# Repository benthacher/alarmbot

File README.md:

# Alarmbot project

## Alarmbot PCB

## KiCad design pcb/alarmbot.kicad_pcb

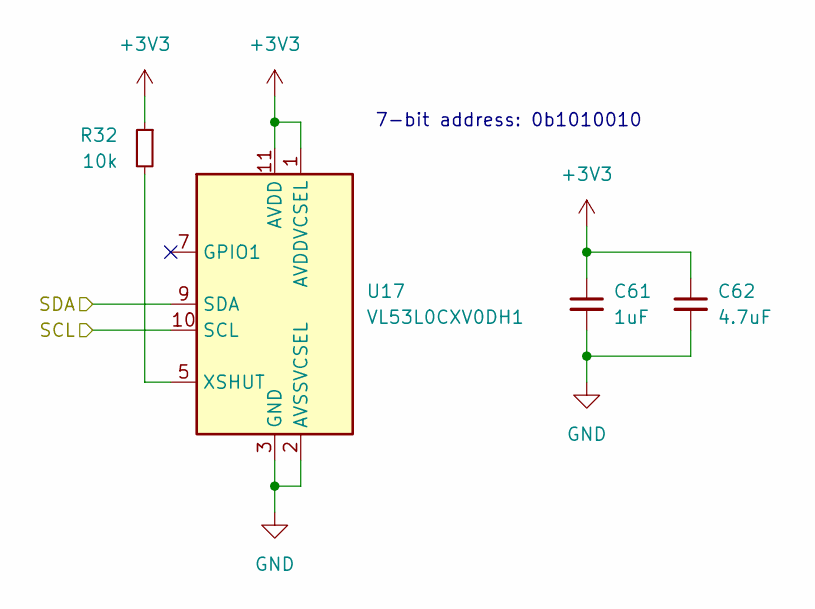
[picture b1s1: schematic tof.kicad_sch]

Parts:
C61: 1uF; C_0402_1005Metric; LCSC C52923
C62: 4.7uF; C_0402_1005Metric; LCSC C23733
R32: 10k; R_0402_1005Metric; LCSC C25744
U17: VL53L0CXV0DH1; ST_VL53L1x; LCSC C91199

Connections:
+3V3: C61.1, C62.1, R32.1, U17.1 (AVDDVCSEL), U17.11 (AVDD); also elsewhere on the board
/MCU/I2C2_SCL: U17.10 (SCL); also elsewhere on the board
/MCU/I2C2_SDA: U17.9 (SDA); also elsewhere on the board
GND: C61.2, C62.2, U17.2 (AVSSVCSEL), U17.3 (GND), U17.4 (GND), U17.6 (GND), U17.12 (GND); also elsewhere on the board
unnamed: R32.2, U17.5 (XSHUT)

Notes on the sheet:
7-bit address: 0b1010010

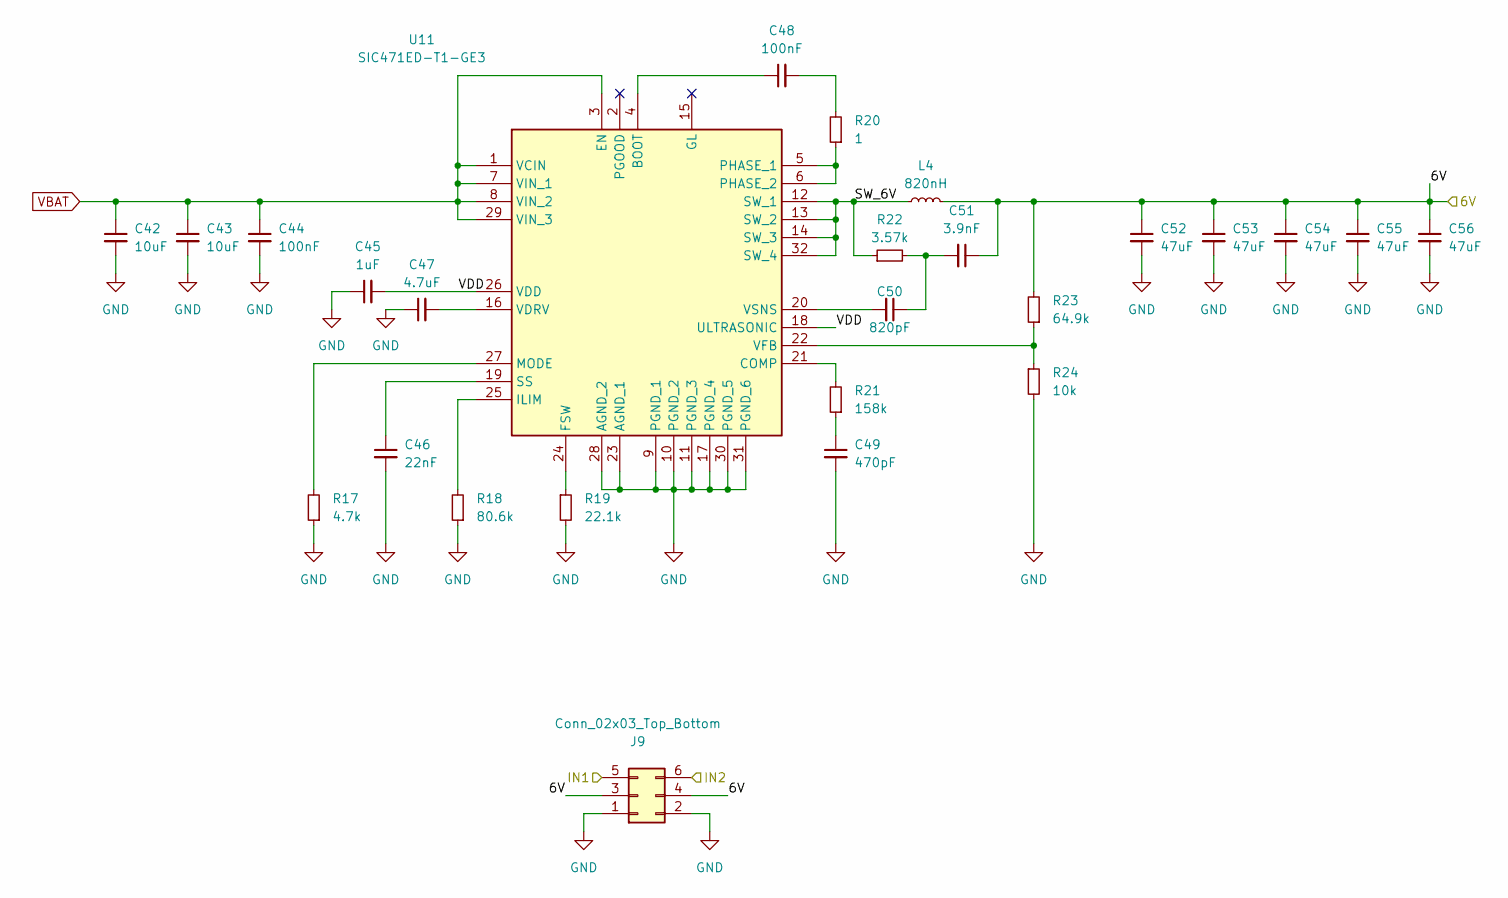
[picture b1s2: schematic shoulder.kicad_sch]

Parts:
C42, C43: 10uF; C_1206_3216Metric; LCSC C13585
C44, C48: 100nF; C_0402_1005Metric; Voltage 50V; LCSC C307331
C45: 1uF; C_0402_1005Metric; LCSC C52923
C46: 22nF; C_0402_1005Metric; LCSC C1532
C47: 4.7uF; C_0402_1005Metric; LCSC C23733
C49: 470pF; C_0402_1005Metric; LCSC C1537
C50: 820pF; C_0402_1005Metric; LCSC C107031
C51: 3.9nF; C_0402_1005Metric; LCSC C45188
C52, C53, C54, C55, C56: 47uF; C_1210_3225Metric; LCSC C5440143
J9: Conn_02x03_Top_Bottom; PinHeader_2x03_P2.54mm_Vertical
L4: 820nH; CMPI1040; LCSC C7588944
R17: 4.7k; R_0402_1005Metric; LCSC C25900
R18: 80.6k; R_0402_1005Metric; LCSC C25921
R19: 22.1k; R_0402_1005Metric; LCSC C43473
R20: 1; R_0402_1005Metric; LCSC C25086
R21: 158k; R_0402_1005Metric; LCSC C185464
R22: 3.57k; R_0402_1005Metric; LCSC C3037168
R23: 64.9k; R_0402_1005Metric; LCSC C5713275
R24: 10k; R_0402_1005Metric; LCSC C25744
U11: SIC471ED-T1-GE3; SIC471EDT1GE3; Manufacturer_Part_Number SIC471ED-T1-GE3; Mouser Part Number 78-SIC471ED-T1-GE3

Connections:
/MCU/TIM2_CH1: J9.5; also elsewhere on the board
/MCU/TIM2_CH2: J9.6; also elsewhere on the board
/Shoulder1/6V: C51.1, C52.1, C53.1, C54.1, C55.1, C56.1, J9.3, J9.4, L4.2, R23.2
/Shoulder1/SW_6V: L4.1, R22.1, U11.12 (SW_1), U11.13 (SW_2), U11.14 (SW_3), U11.32 (SW_4)
/Shoulder1/VDD: C45.2, U11.18 (ULTRASONIC), U11.26 (VDD)
GND: C42.2, C43.2, C44.2, C45.1, C46.2, C47.1, C49.2, C52.2, C53.2, C54.2, C55.2, C56.2, J9.1, J9.2, R17.1, R18.1, R19.2, R24.2, U11.9 (PGND_1), U11.10 (PGND_2), U11.11 (PGND_3), U11.17 (PGND_4), U11.23 (AGND_1), U11.28 (AGND_2), U11.30 (PGND_5), U11.31 (PGND_6); also elsewhere on the board
unnamed: C48.2, R20.2
unnamed: C49.1, R21.1
unnamed: C50.1, C51.2, R22.2
unnamed: C48.1, U11.4 (BOOT)
unnamed: R21.2, U11.21 (COMP)
unnamed: R19.1, U11.24 (FSW)
unnamed: R18.2, U11.25 (ILIM)
unnamed: R17.2, U11.27 (MODE)
unnamed: R20.1, U11.5 (PHASE_1), U11.6 (PHASE_2)
unnamed: C46.1, U11.19 (SS)
unnamed: C47.2, U11.16 (VDRV)
unnamed: R23.1, R24.1, U11.22 (VFB)
unnamed: C50.2, U11.20 (VSNS)
VBAT: C42.1, C43.1, C44.1, U11.1 (VCIN), U11.3 (EN), U11.7 (VIN_1), U11.8 (VIN_2), U11.29 (VIN_3); also elsewhere on the board

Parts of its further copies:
C63, C64, C78, C79, C93, C94: 10uF; C_1206_3216Metric; LCSC C13585
C65, C69, C80, C84, C95, C99: 100nF; C_0402_1005Metric; Voltage 50V; LCSC C307331
C66, C81, C96: 1uF; C_0402_1005Metric; LCSC C52923
C67, C82, C97: 22nF; C_0402_1005Metric; LCSC C1532
C68, C83, C98: 4.7uF; C_0402_1005Metric; LCSC C23733
C70, C85, C100: 470pF; C_0402_1005Metric; LCSC C1537
C71, C86, C101: 820pF; C_0402_1005Metric; LCSC C107031
C72, C87, C102: 3.9nF; C_0402_1005Metric; LCSC C45188
C73, C74, C75, C76, C77, C88, C89, C90, C91, C92, C103, C104, C105, C106, C107: 47uF; C_1210_3225Metric; LCSC C5440143
J13, J14, J15: Conn_02x03_Top_Bottom; PinHeader_2x03_P2.54mm_Vertical
L5, L6, L7: 820nH; CMPI1040; LCSC C7588944
R33, R41, R49: 4.7k; R_0402_1005Metric; LCSC C25900
R34, R42, R50: 80.6k; R_0402_1005Metric; LCSC C25921
R35, R43, R51: 22.1k; R_0402_1005Metric; LCSC C43473
R36, R44, R52: 1; R_0402_1005Metric; LCSC C25086
R37, R45, R53: 158k; R_0402_1005Metric; LCSC C185464
R38, R46, R54: 3.57k; R_0402_1005Metric; LCSC C3037168
R39, R47, R55: 64.9k; R_0402_1005Metric; LCSC C5713275
R40, R48, R56: 10k; R_0402_1005Metric; LCSC C25744
U18, U19, U20: SIC471ED-T1-GE3; SIC471EDT1GE3; Manufacturer_Part_Number SIC471ED-T1-GE3; Mouser Part Number 78-SIC471ED-T1-GE3

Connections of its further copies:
/MCU/TIM1_CH1: J14.5; also elsewhere on the board
/MCU/TIM1_CH2: J14.6; also elsewhere on the board
/MCU/TIM1_CH3: J15.5; also elsewhere on the board
/MCU/TIM1_CH4: J15.6; also elsewhere on the board
/MCU/TIM2_CH3: J13.5; also elsewhere on the board
/MCU/TIM2_CH4: J13.6; also elsewhere on the board
/Shoulder2/6V: C72.1, C73.1, C74.1, C75.1, C76.1, C77.1, J13.3, J13.4, L5.2, R39.2; also elsewhere on the board
/Shoulder2/SW_6V: L5.1, R38.1, U18.12 (SW_1), U18.13 (SW_2), U18.14 (SW_3), U18.32 (SW_4)
/Shoulder2/VDD: C66.2, U18.18 (ULTRASONIC), U18.26 (VDD)
/Shoulder3/6V: C87.1, C88.1, C89.1, C90.1, C91.1, C92.1, J14.3, J14.4, L6.2, R47.2
/Shoulder3/SW_6V: L6.1, R46.1, U19.12 (SW_1), U19.13 (SW_2), U19.14 (SW_3), U19.32 (SW_4)
/Shoulder3/VDD: C81.2, U19.18 (ULTRASONIC), U19.26 (VDD)
/Shoulder4/6V: C102.1, C103.1, C104.1, C105.1, C106.1, C107.1, J15.3, J15.4, L7.2, R55.2; also elsewhere on the board
/Shoulder4/SW_6V: L7.1, R54.1, U20.12 (SW_1), U20.13 (SW_2), U20.14 (SW_3), U20.32 (SW_4)
/Shoulder4/VDD: C96.2, U20.18 (ULTRASONIC), U20.26 (VDD)
GND: C63.2, C64.2, C65.2, C66.1, C67.2, C68.1, C70.2, C73.2, C74.2, C75.2, C76.2, C77.2, C78.2, C79.2, C80.2, C81.1, C82.2, C83.1, C85.2, C88.2, C89.2, C90.2, C91.2, C92.2, C93.2, C94.2, C95.2, C96.1, C97.2, C98.1, C100.2, C103.2, C104.2, C105.2, C106.2, C107.2, J13.1, J13.2, J14.1, J14.2, J15.1, J15.2, R33.1, R34.1, R35.2, R40.2, R41.1, R42.1, R43.2, R48.2, R49.1, R50.1, R51.2, R56.2, U18.9 (PGND_1), U18.10 (PGND_2), U18.11 (PGND_3), U18.17 (PGND_4), U18.23 (AGND_1), U18.28 (AGND_2), U18.30 (PGND_5), U18.31 (PGND_6), U19.9 (PGND_1), U19.10 (PGND_2), U19.11 (PGND_3), U19.17 (PGND_4), U19.23 (AGND_1), U19.28 (AGND_2), U19.30 (PGND_5), U19.31 (PGND_6), U20.9 (PGND_1), U20.10 (PGND_2), U20.11 (PGND_3), U20.17 (PGND_4), U20.23 (AGND_1), U20.28 (AGND_2), U20.30 (PGND_5), U20.31 (PGND_6); also elsewhere on the board
unnamed: C69.2, R36.2
unnamed: C70.1, R37.1
unnamed: C71.1, C72.2, R38.2
unnamed: C84.2, R44.2
unnamed: C85.1, R45.1
unnamed: C86.1, C87.2, R46.2
unnamed: C99.2, R52.2
unnamed: C100.1, R53.1
unnamed: C101.1, C102.2, R54.2
unnamed: C69.1, U18.4 (BOOT)
unnamed: R37.2, U18.21 (COMP)
unnamed: R35.1, U18.24 (FSW)
unnamed: R34.2, U18.25 (ILIM)
unnamed: R33.2, U18.27 (MODE)
unnamed: R36.1, U18.5 (PHASE_1), U18.6 (PHASE_2)
unnamed: C67.1, U18.19 (SS)
unnamed: C68.2, U18.16 (VDRV)
unnamed: R39.1, R40.1, U18.22 (VFB)
unnamed: C71.2, U18.20 (VSNS)
unnamed: C84.1, U19.4 (BOOT)
unnamed: R45.2, U19.21 (COMP)
unnamed: R43.1, U19.24 (FSW)
unnamed: R42.2, U19.25 (ILIM)
unnamed: R41.2, U19.27 (MODE)
unnamed: R44.1, U19.5 (PHASE_1), U19.6 (PHASE_2)
unnamed: C82.1, U19.19 (SS)
unnamed: C83.2, U19.16 (VDRV)
unnamed: R47.1, R48.1, U19.22 (VFB)
unnamed: C86.2, U19.20 (VSNS)
unnamed: C99.1, U20.4 (BOOT)
unnamed: R53.2, U20.21 (COMP)
unnamed: R51.1, U20.24 (FSW)
unnamed: R50.2, U20.25 (ILIM)
unnamed: R49.2, U20.27 (MODE)
unnamed: R52.1, U20.5 (PHASE_1), U20.6 (PHASE_2)
unnamed: C97.1, U20.19 (SS)
unnamed: C98.2, U20.16 (VDRV)
unnamed: R55.1, R56.1, U20.22 (VFB)
unnamed: C101.2, U20.20 (VSNS)
VBAT: C63.1, C64.1, C65.1, C78.1, C79.1, C80.1, C93.1, C94.1, C95.1, U18.1 (VCIN), U18.3 (EN), U18.7 (VIN_1), U18.8 (VIN_2), U18.29 (VIN_3), U19.1 (VCIN), U19.3 (EN), U19.7 (VIN_1), U19.8 (VIN_2), U19.29 (VIN_3), U20.1 (VCIN), U20.3 (EN), U20.7 (VIN_1), U20.8 (VIN_2), U20.29 (VIN_3); also elsewhere on the board

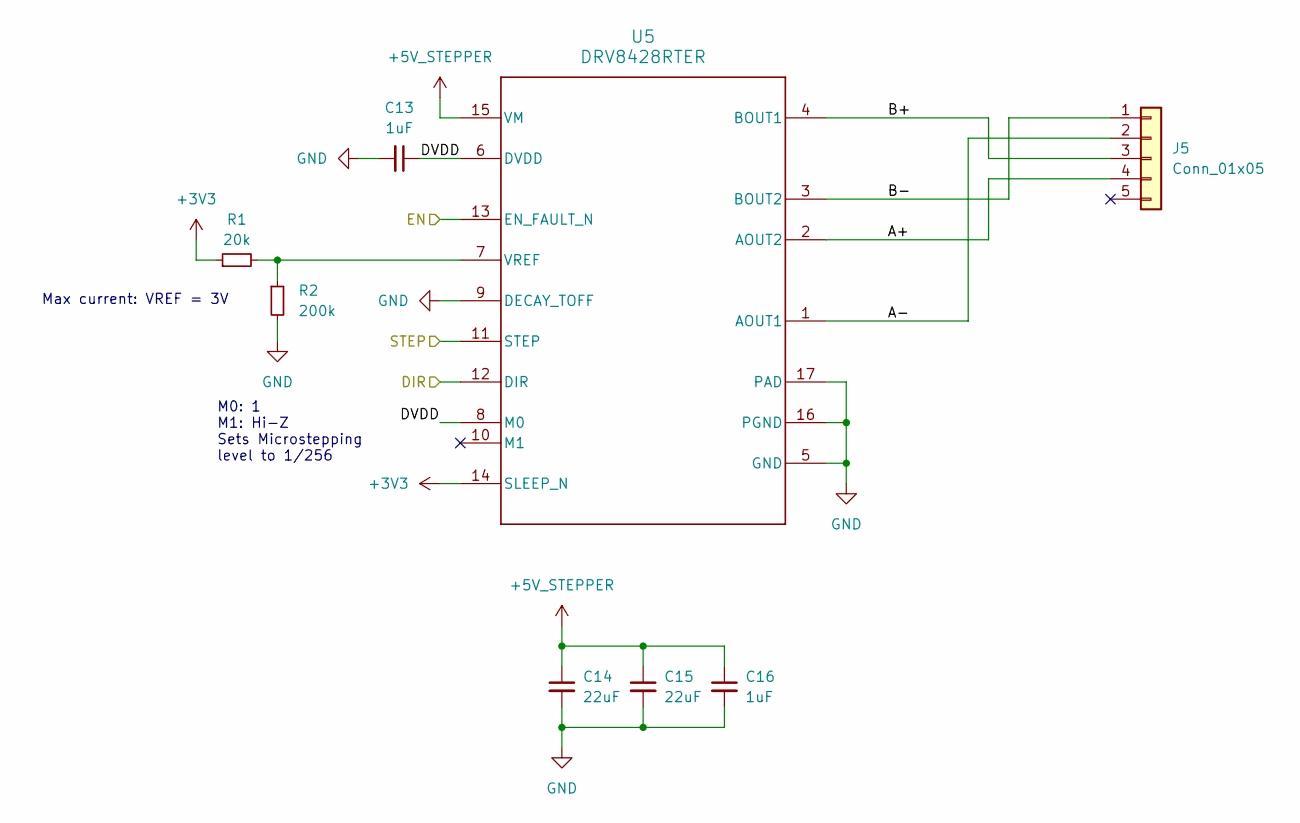
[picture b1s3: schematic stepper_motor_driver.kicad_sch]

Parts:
C13, C16: 1uF; C_0402_1005Metric; LCSC C52923
C14, C15: 22uF; C_1206_3216Metric; LCSC C12891
J5: Conn_01x05; JST_XH_B5B-XH-A_1x05_P2.50mm_Vertical
R1: 20k; R_0402_1005Metric; LCSC C25765
R2: 200k; R_0402_1005Metric; LCSC C25764
U5: DRV8428RTER; RTE0016J; LCSC C2857955

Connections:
+3V3: R1.1, U5.14 (SLEEP_N); also elsewhere on the board
+5V_STEPPER: C14.1, C15.1, C16.1, U5.15 (VM); also elsewhere on the board
/MCU/HEAD_PITCH_DIR: U5.12 (DIR); also elsewhere on the board
/MCU/HEAD_PITCH_EN: U5.13 (EN_FAULT_N); also elsewhere on the board
/MCU/TIM17_CH1: U5.11 (STEP); also elsewhere on the board
/Stepper1/A+: J5.4, U5.2 (AOUT2)
/Stepper1/A-: J5.2, U5.1 (AOUT1)
/Stepper1/B+: J5.3, U5.4 (BOUT1)
/Stepper1/B-: J5.1, U5.3 (BOUT2)
/Stepper1/DVDD: C13.1, U5.6 (DVDD), U5.8 (M0)
GND: C13.2, C14.2, C15.2, C16.2, R2.2, U5.5 (GND), U5.9 (DECAY_TOFF), U5.16 (PGND), U5.17 (PAD); also elsewhere on the board
unnamed: R1.2, R2.1, U5.7 (VREF)

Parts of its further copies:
C24, C27: 1uF; C_0402_1005Metric; LCSC C52923
C25, C26: 22uF; C_1206_3216Metric; LCSC C12891
J7: Conn_01x05; JST_XH_B5B-XH-A_1x05_P2.50mm_Vertical
R6: 20k; R_0402_1005Metric; LCSC C25765
R7: 200k; R_0402_1005Metric; LCSC C25764
U7: DRV8428RTER; RTE0016J; LCSC C2857955

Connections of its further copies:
+3V3: R6.1, U7.14 (SLEEP_N); also elsewhere on the board
+5V_STEPPER: C25.1, C26.1, C27.1, U7.15 (VM); also elsewhere on the board
/MCU/HEAD_YAW_DIR: U7.12 (DIR); also elsewhere on the board
/MCU/HEAD_YAW_EN: U7.13 (EN_FAULT_N); also elsewhere on the board
/MCU/TIM16_CH1: U7.11 (STEP); also elsewhere on the board
/Stepper2/A+: J7.4, U7.2 (AOUT2)
/Stepper2/A-: J7.2, U7.1 (AOUT1)
/Stepper2/B+: J7.3, U7.4 (BOUT1)
/Stepper2/B-: J7.1, U7.3 (BOUT2)
/Stepper2/DVDD: C24.1, U7.6 (DVDD), U7.8 (M0)
GND: C24.2, C25.2, C26.2, C27.2, R7.2, U7.5 (GND), U7.9 (DECAY_TOFF), U7.16 (PGND), U7.17 (PAD); also elsewhere on the board
unnamed: R6.2, R7.1, U7.7 (VREF)

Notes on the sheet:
M0: 1 M1: Hi-Z Sets Microstepping level to 1/256
Max current: VREF = 3V

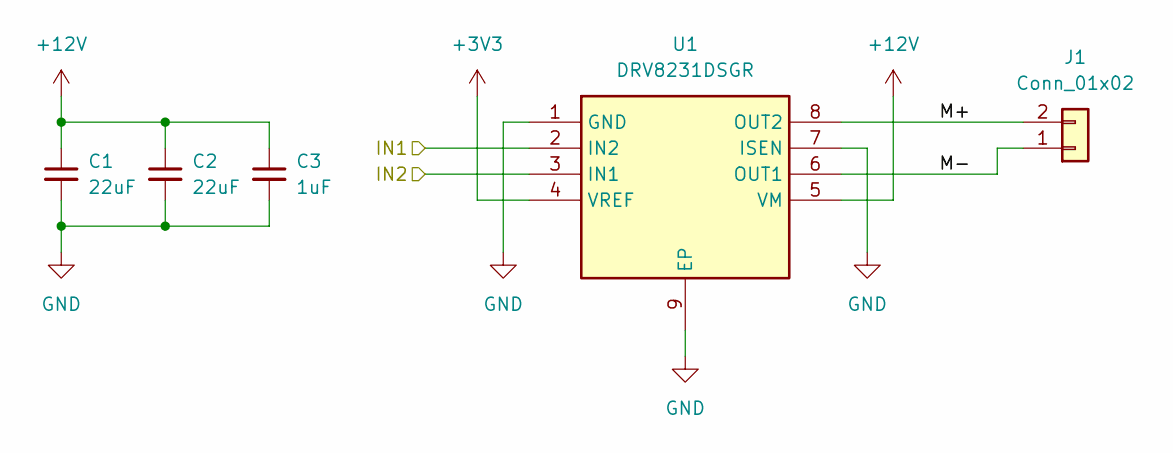
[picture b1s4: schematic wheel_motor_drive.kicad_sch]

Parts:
C1, C2: 22uF; C_1206_3216Metric; LCSC C12891
C3: 1uF; C_0402_1005Metric; LCSC C52923
J1: Conn_01x02; JST_VH_S2P-VH_1x02_P3.96mm_Horizontal; LCSC C158007
U1: DRV8231DSGR; SON50P200X200X80-9N; Manufacturer_Part_Number DRV8231DSGR; Mouser Part Number 595-DRV8231DSGR

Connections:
+3V3: U1.4 (VREF); also elsewhere on the board
+12V: C1.1, C2.1, C3.1, U1.5 (VM); also elsewhere on the board
/MCU/TIM3_CH1: U1.2 (IN2); also elsewhere on the board
/MCU/TIM3_CH2: U1.3 (IN1); also elsewhere on the board
/Wheel1/M+: J1.2, U1.8 (OUT2)
/Wheel1/M-: J1.1, U1.6 (OUT1)
GND: C1.2, C2.2, C3.2, U1.1 (GND), U1.7 (ISEN), U1.9 (EP); also elsewhere on the board

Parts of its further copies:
C4, C5, C7, C8, C10, C11: 22uF; C_1206_3216Metric; LCSC C12891
C6, C9, C12: 1uF; C_0402_1005Metric; LCSC C52923
J2, J3, J4: Conn_01x02; JST_VH_S2P-VH_1x02_P3.96mm_Horizontal; LCSC C158007
U2, U3, U4: DRV8231DSGR; SON50P200X200X80-9N; Manufacturer_Part_Number DRV8231DSGR; Mouser Part Number 595-DRV8231DSGR

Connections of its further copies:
+3V3: U2.4 (VREF), U3.4 (VREF), U4.4 (VREF); also elsewhere on the board
+12V: C4.1, C5.1, C6.1, C7.1, C8.1, C9.1, C10.1, C11.1, C12.1, U2.5 (VM), U3.5 (VM), U4.5 (VM); also elsewhere on the board
/MCU/TIM3_CH3: U2.2 (IN2); also elsewhere on the board
/MCU/TIM3_CH4: U2.3 (IN1); also elsewhere on the board
/MCU/TIM4_CH1: U3.2 (IN2); also elsewhere on the board
/MCU/TIM4_CH2: U3.3 (IN1); also elsewhere on the board
/MCU/TIM4_CH3: U4.2 (IN2); also elsewhere on the board
/MCU/TIM4_CH4: U4.3 (IN1); also elsewhere on the board
/Wheel2/M+: J2.2, U2.8 (OUT2)
/Wheel2/M-: J2.1, U2.6 (OUT1)
/Wheel3/M+: J3.2, U3.8 (OUT2)
/Wheel3/M-: J3.1, U3.6 (OUT1)
/Wheel4/M+: J4.2, U4.8 (OUT2)
/Wheel4/M-: J4.1, U4.6 (OUT1)
GND: C4.2, C5.2, C6.2, C7.2, C8.2, C9.2, C10.2, C11.2, C12.2, U2.1 (GND), U2.7 (ISEN), U2.9 (EP), U3.1 (GND), U3.7 (ISEN), U3.9 (EP), U4.1 (GND), U4.7 (ISEN), U4.9 (EP); also elsewhere on the board

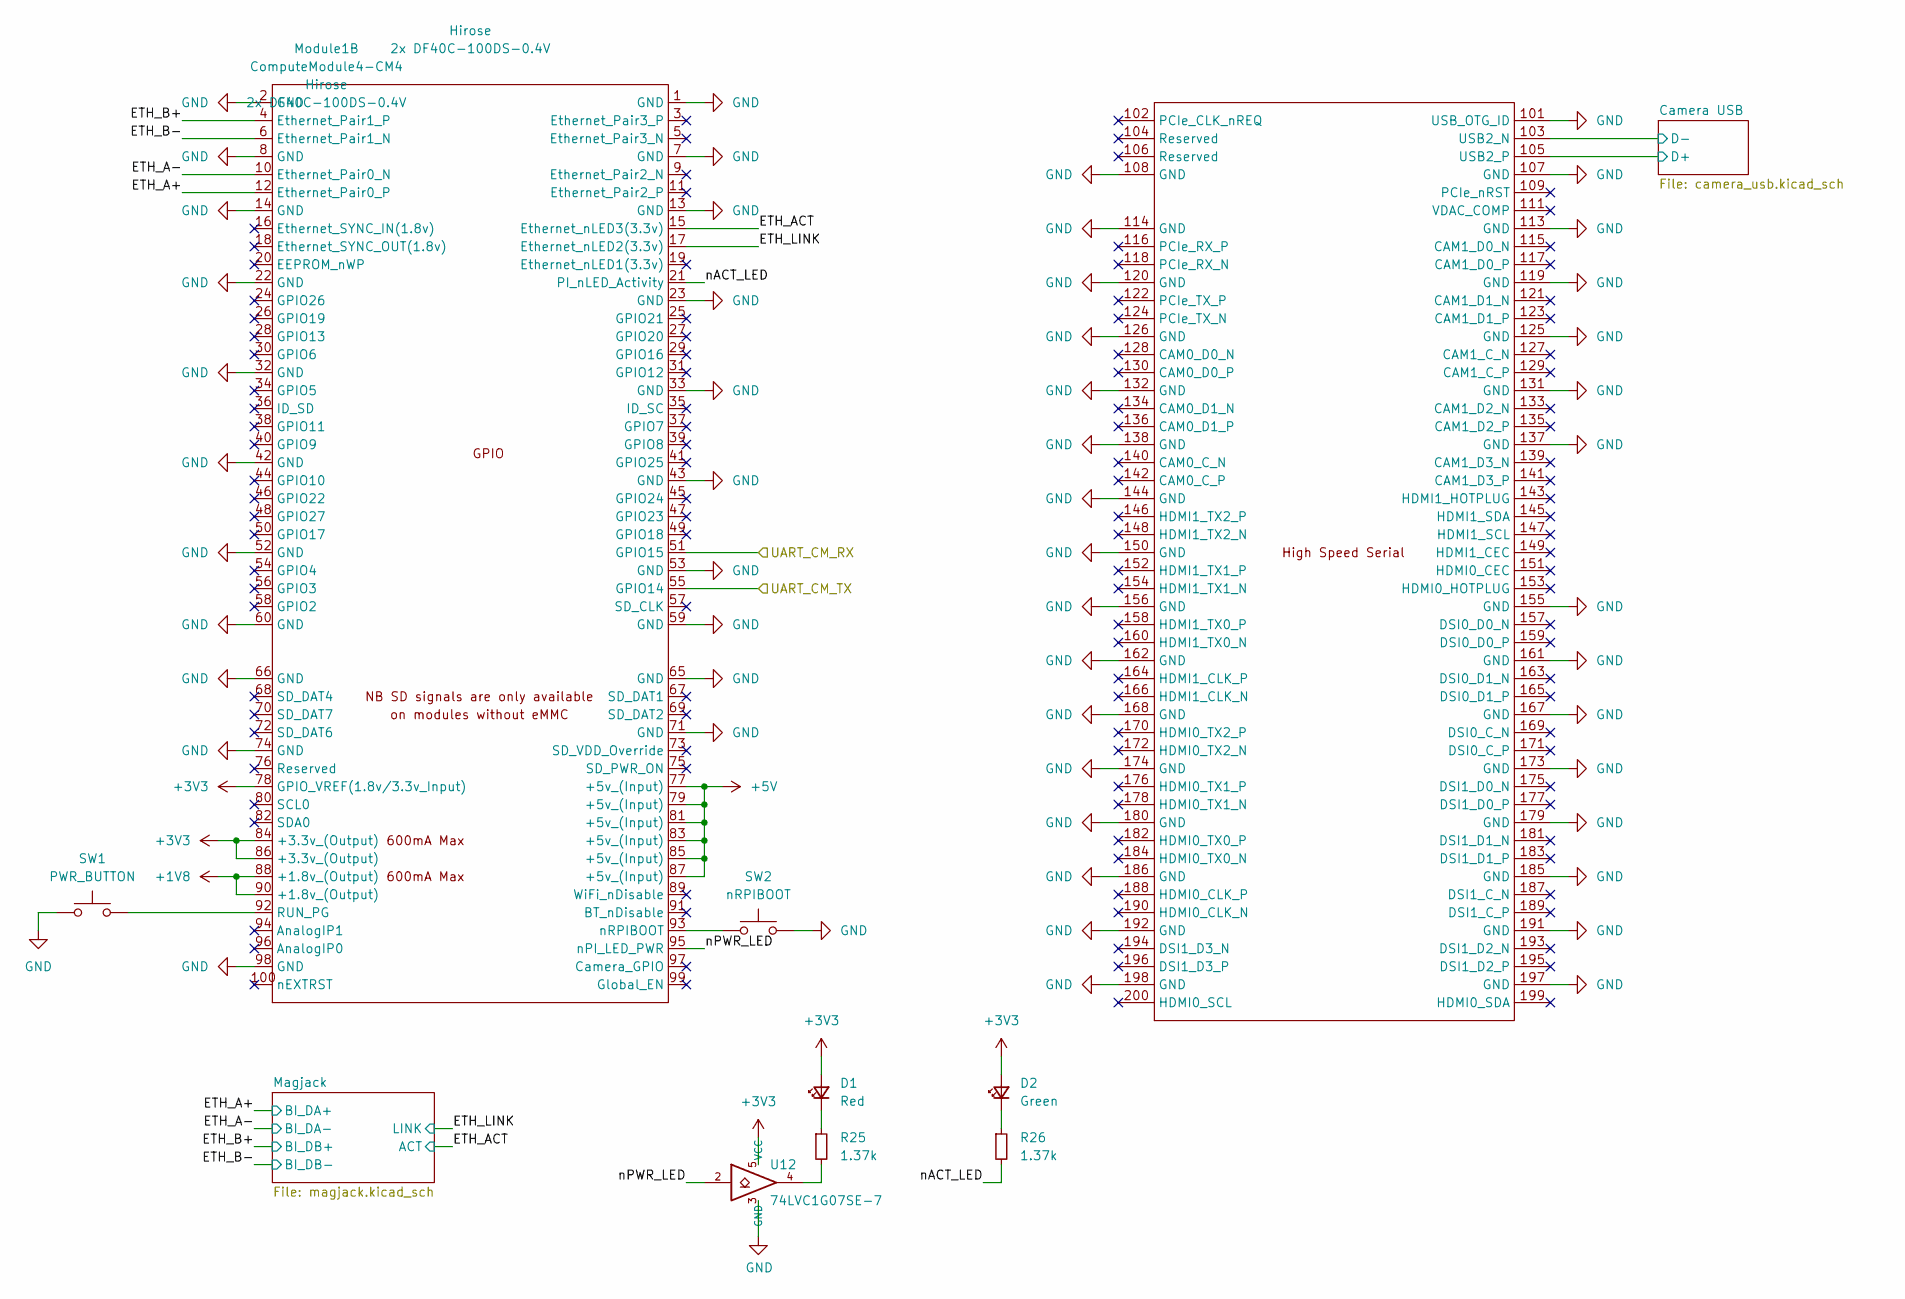
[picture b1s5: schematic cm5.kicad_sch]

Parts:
D1: Red; LED_0402_1005Metric; LCSC C264407
D2: Green; LED_0402_1005Metric; LCSC C401111
Module1: ComputeModule4-CM4; Raspberry-Pi-4-Compute-Module
R25, R26: 1.37k; R_0402_1005Metric; LCSC C321297
SW1: PWR_BUTTON; TL1017ABAF160QG
SW2: nRPIBOOT; TL1017ABAF160QG
U12: 74LVC1G07SE-7; SOT-353_SC-70-5; Part Description Buffer, Non-Inverting 1 Element 1 Bit p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; LCSC C264081

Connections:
+1V8: Module1.88 (+1.8v_(Output)), Module1.90 (+1.8v_(Output)); also elsewhere on the board
+3V3: D1.2 (A), D2.2 (A), Module1.78 (GPIO_VREF(1.8v/3.3v_Input)), Module1.84 (+3.3v_(Output)), Module1.86 (+3.3v_(Output)), U12.5 (VCC); also elsewhere on the board
+5V: Module1.77 (+5v_(Input)), Module1.79 (+5v_(Input)), Module1.81 (+5v_(Input)), Module1.83 (+5v_(Input)), Module1.85 (+5v_(Input)), Module1.87 (+5v_(Input)); also elsewhere on the board
/MCU/USART3_RX: Module1.55 (GPIO14); also elsewhere on the board
/MCU/USART3_TX: Module1.51 (GPIO15); also elsewhere on the board
/cm5/Camera USB/D+: Module1.105 (USB2_P); also elsewhere on the board
/cm5/Camera USB/D-: Module1.103 (USB2_N); also elsewhere on the board
/cm5/ETH_A+: Module1.12 (Ethernet_Pair0_P); also elsewhere on the board
/cm5/ETH_A-: Module1.10 (Ethernet_Pair0_N); also elsewhere on the board
/cm5/ETH_ACT: Module1.15 (Ethernet_nLED3(3.3v)); also elsewhere on the board
/cm5/ETH_B+: Module1.4 (Ethernet_Pair1_P); also elsewhere on the board
/cm5/ETH_B-: Module1.6 (Ethernet_Pair1_N); also elsewhere on the board
/cm5/ETH_LINK: Module1.17 (Ethernet_nLED2(3.3v)); also elsewhere on the board
/cm5/nACT_LED: Module1.21 (PI_nLED_Activity), R26.2
/cm5/nPWR_LED: Module1.95 (nPI_LED_PWR), U12.2
GND: Module1.1 (GND), Module1.2 (GND), Module1.7 (GND), Module1.8 (GND), Module1.13 (GND), Module1.14 (GND), Module1.22 (GND), Module1.23 (GND), Module1.32 (GND), Module1.33 (GND), Module1.42 (GND), Module1.43 (GND), Module1.52 (GND), Module1.53 (GND), Module1.59 (GND), Module1.60 (GND), Module1.65 (GND), Module1.66 (GND), Module1.71 (GND), Module1.74 (GND), Module1.98 (GND), Module1.101 (USB_OTG_ID), Module1.107 (GND), Module1.108 (GND), Module1.113 (GND), Module1.114 (GND), Module1.119 (GND), Module1.120 (GND), Module1.125 (GND), Module1.126 (GND), Module1.131 (GND), Module1.132 (GND), Module1.137 (GND), Module1.138 (GND), Module1.144 (GND), Module1.150 (GND), Module1.155 (GND), Module1.156 (GND), Module1.161 (GND), Module1.162 (GND), Module1.167 (GND), Module1.168 (GND), Module1.173 (GND), Module1.174 (GND), Module1.179 (GND), Module1.180 (GND), Module1.185 (GND), Module1.186 (GND), Module1.191 (GND), Module1.192 (GND), Module1.197 (GND), Module1.198 (GND), SW1.1, SW2.2, U12.3 (GND); also elsewhere on the board
unnamed: D1.1 (K), R25.1
unnamed: D2.1 (K), R26.1
unnamed: Module1.92 (RUN_PG), SW1.2
unnamed: Module1.93 (nRPIBOOT), SW2.1
unnamed: R25.2, U12.4

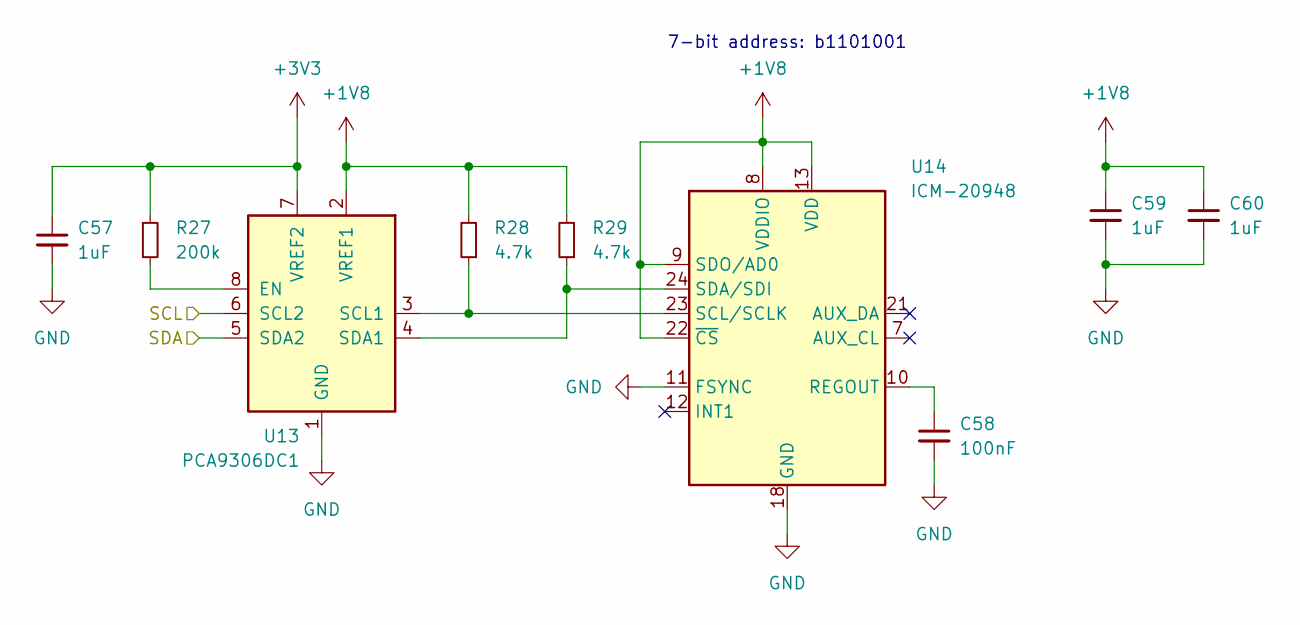
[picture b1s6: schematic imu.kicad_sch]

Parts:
C57, C59, C60: 1uF; C_0402_1005Metric; LCSC C52923
C58: 100nF; C_0402_1005Metric; Voltage 50V; LCSC C307331
R27: 200k; R_0402_1005Metric; LCSC C25764
R28, R29: 4.7k; R_0402_1005Metric; LCSC C25900
U13: PCA9306DC1; VSSOP-8_2.3x2mm_P0.5mm; LCSC C129510
U14: ICM-20948; InvenSense_QFN-24_3x3mm_P0.4mm; LCSC C726001

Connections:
+1V8: C59.1, C60.1, R28.2, R29.2, U13.2 (VREF1), U14.8 (VDDIO), U14.9 (SDO/AD0), U14.13 (VDD), U14.22 (~CS); also elsewhere on the board
+3V3: C57.1, R27.1, U13.7 (VREF2); also elsewhere on the board
/MCU/I2C2_SCL: U13.6 (SCL2); also elsewhere on the board
/MCU/I2C2_SDA: U13.5 (SDA2); also elsewhere on the board
GND: C57.2, C58.2, C59.2, C60.2, U13.1 (GND), U14.11 (FSYNC), U14.18 (GND), U14.20 (GND); also elsewhere on the board
unnamed: R27.2, U13.8 (EN)
unnamed: R28.1, U13.3 (SCL1), U14.23 (SCL/SCLK)
unnamed: R29.1, U13.4 (SDA1), U14.24 (SDA/SDI)
unnamed: C58.1, U14.10 (REGOUT)

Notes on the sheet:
7-bit address: b1101001

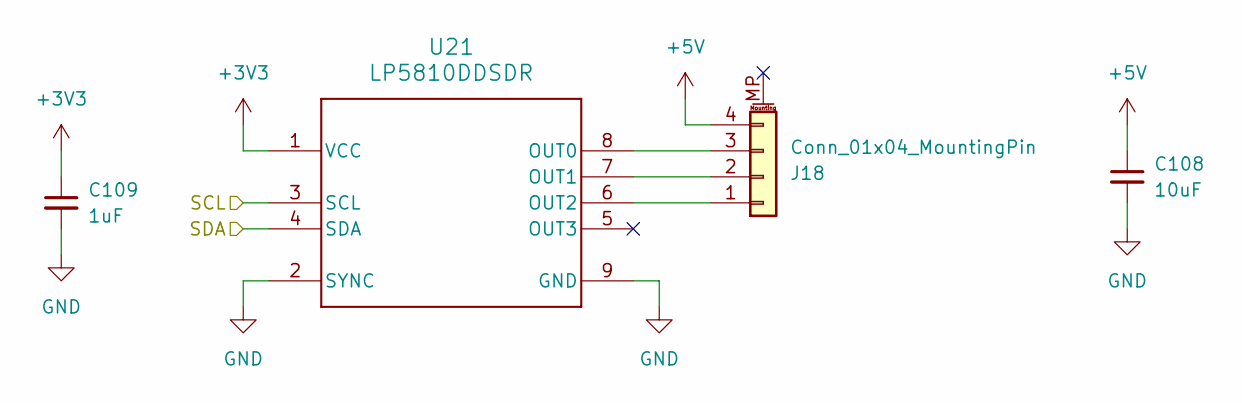
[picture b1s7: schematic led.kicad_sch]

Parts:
C108: 10uF; C_0603_1608Metric; Voltage 10V; LCSC C19702
C109: 1uF; C_0402_1005Metric; LCSC C52923
J18: Conn_01x04_MountingPin; JST_SH_BM04B-SRSS-TB_1x04-1MP_P1.00mm_Vertical; LCSC C160390
U21: LP5810DDSDR; DSD0008B-IPC_A; LCSC C32392783

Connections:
+3V3: C109.1, U21.1 (VCC); also elsewhere on the board
+5V: C108.1, J18.4; also elsewhere on the board
/MCU/I2C2_SCL: U21.3 (SCL); also elsewhere on the board
/MCU/I2C2_SDA: U21.4 (SDA); also elsewhere on the board
GND: C108.2, C109.2, U21.2 (SYNC), U21.9 (GND); also elsewhere on the board
unnamed: J18.1, U21.6 (OUT2)
unnamed: J18.2, U21.7 (OUT1)
unnamed: J18.3, U21.8 (OUT0)

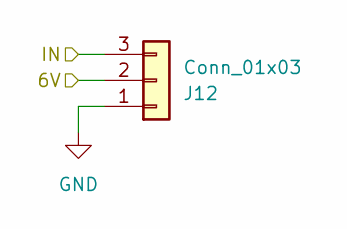
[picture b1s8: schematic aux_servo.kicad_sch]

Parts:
J12: Conn_01x03; PinHeader_1x03_P2.54mm_Vertical

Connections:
/MCU/TIM15_CH1: J12.3; also elsewhere on the board
/Shoulder2/6V: J12.2; also elsewhere on the board
GND: J12.1; also elsewhere on the board

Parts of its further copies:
J16: Conn_01x03; PinHeader_1x03_P2.54mm_Vertical

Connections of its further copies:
/MCU/TIM15_CH2: J16.3; also elsewhere on the board
/Shoulder4/6V: J16.2; also elsewhere on the board
GND: J16.1; also elsewhere on the board

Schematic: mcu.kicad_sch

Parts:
C17, C18, C19, C20, C21, C22: 1uF; C_0402_1005Metric; LCSC C52923
C23: 4.7uF; C_0402_1005Metric; LCSC C23733
J6: Conn_ARM_JTAG_SWD_10; FTSH-105-XX-YYY-DV-K-P; LCSC C19191729
R3: 100k; R_0402_1005Metric; LCSC C25741
R4, R5: 4.7k; R_0402_1005Metric; LCSC C25900
U6: STM32G431CBUx; QFN-48-1EP_7x7mm_P0.5mm_EP5.6x5.6mm; LCSC C529356

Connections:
+3V3: C17.1, C18.1, C19.1, C20.1, C21.1, C22.1, C23.1, J6.1 (VTref), R4.2, R5.2, U6.1 (VBAT), U6.20 (VREF+), U6.21 (VDDA), U6.23 (VDD), U6.35 (VDD), U6.48 (VDD); also elsewhere on the board
/MCU/HEAD_PITCH_DIR: U6.14 (PA6); also elsewhere on the board
/MCU/HEAD_PITCH_EN: U6.13 (PA5); also elsewhere on the board
/MCU/HEAD_YAW_DIR: U6.41 (PB3); also elsewhere on the board
/MCU/HEAD_YAW_EN: U6.40 (PC11); also elsewhere on the board
/MCU/I2C2_SCL: R5.1, U6.16 (PC4); also elsewhere on the board
/MCU/I2C2_SDA: R4.1, U6.5 (PF0); also elsewhere on the board
/MCU/NRST: J6.10 (~RESET), U6.7 (PG10)
/MCU/SWCLK: J6.4 (SWCLK/TCK), U6.37 (PA14)
/MCU/SWDIO: J6.2 (SWDIO/TMS), U6.36 (PA13)
/MCU/TIM1_CH1: U6.30 (PA8); also elsewhere on the board
/MCU/TIM1_CH2: U6.31 (PA9); also elsewhere on the board
/MCU/TIM1_CH3: U6.32 (PA10); also elsewhere on the board
/MCU/TIM1_CH4: U6.33 (PA11); also elsewhere on the board
/MCU/TIM2_CH1: U6.8 (PA0); also elsewhere on the board
/MCU/TIM2_CH2: U6.9 (PA1); also elsewhere on the board
/MCU/TIM2_CH3: U6.10 (PA2); also elsewhere on the board
/MCU/TIM2_CH4: U6.11 (PA3); also elsewhere on the board
/MCU/TIM3_CH1: U6.29 (PC6); also elsewhere on the board
/MCU/TIM3_CH2: U6.12 (PA4); also elsewhere on the board
/MCU/TIM3_CH3: U6.17 (PB0); also elsewhere on the board
/MCU/TIM3_CH4: U6.18 (PB1); also elsewhere on the board
/MCU/TIM4_CH1: U6.44 (PB6); also elsewhere on the board
/MCU/TIM4_CH2: U6.45 (PB7); also elsewhere on the board
/MCU/TIM4_CH3: R3.2, U6.46 (PB8); also elsewhere on the board
/MCU/TIM4_CH4: U6.47 (PB9); also elsewhere on the board
/MCU/TIM15_CH1: U6.27 (PB14); also elsewhere on the board
/MCU/TIM15_CH2: U6.28 (PB15); also elsewhere on the board
/MCU/TIM16_CH1: U6.42 (PB4); also elsewhere on the board
/MCU/TIM17_CH1: U6.15 (PA7); also elsewhere on the board
/MCU/USART3_RX: U6.24 (PB11); also elsewhere on the board
/MCU/USART3_TX: U6.22 (PB10); also elsewhere on the board
GND: C17.2, C18.2, C19.2, C20.2, C21.2, C22.2, C23.2, J6.3 (GND), J6.5 (GND), J6.9 (GNDDetect), R3.1, U6.49 (VSS); also elsewhere on the board

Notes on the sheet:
BOOT0

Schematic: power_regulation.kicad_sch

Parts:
C28, C31, C35: 4.7uF; C_1206_3216Metric; LCSC C29823
C29, C30, C32, C34, C36, C40: 100nF; C_0402_1005Metric; Voltage 50V; LCSC C307331
C33, C41: 47uF; C_1210_3225Metric; LCSC C5440143
C37, C38, C39: 22uF; C_1206_3216Metric; LCSC C12891
D3: SMBJ24A; D_SMB
J8: Conn_01x02; TerminalBlock_Phoenix_PT-1,5-2-5.0-H_1x02_P5.00mm_Horizontal
L1, L3: 3.3uH; L_Chilisin_BMRx00060630; LCSC C2838324
L2: 6.8uH; ZEMS0850; LCSC C2051933
R8, R14: 13.3k; R_0402_1005Metric; LCSC C2974007
R9, R12, R15: 100k; R_0402_1005Metric; LCSC C25741
R10, R16: 19.1k; R_0402_1005Metric; LCSC C52036
R11: 24.9k; R_0402_1005Metric; LCSC C2998048
R13: 7.15k; R_0402_1005Metric; LCSC C270586
U8, U9, U10: LMR51450SDRRR; Manufacturer_Part_Number LMR51450SDRRR; Mouser Part Number 595-LMR51450SDRRR

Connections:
+5V: C33.1, L1.2, R9.2; also elsewhere on the board
+5V_STEPPER: C41.1, L3.2, R15.2; also elsewhere on the board
+12V: C37.1, C38.1, C39.1, L2.2, R12.2; also elsewhere on the board
/Power Regulation/SW_5V: C30.2, L1.1, U8.1 (SW), U8.2 (SW_2), U8.3 (SW_3)
/Power Regulation/SW_5V_STEPPER: C40.2, L3.1, U10.1 (SW), U10.2 (SW_2), U10.3 (SW_3)
/Power Regulation/SW_12V: C34.2, L2.1, U9.1 (SW), U9.2 (SW_2), U9.3 (SW_3)
GND: C28.2, C29.1, C31.2, C32.1, C33.2, C35.2, C36.1, C37.2, C38.2, C39.2, C41.2, D3.2 (A), J8.1, R8.2, R10.1, R11.2, R13.1, R14.2, R16.1, U8.8 (AGND), U8.13 (PGND), U9.8 (AGND), U9.13 (PGND), U10.8 (AGND), U10.13 (PGND); also elsewhere on the board
unnamed: C30.1, U8.4 (BOOT)
unnamed: R9.1, R10.2, U8.7 (FB)
unnamed: R8.1, U8.6 (RT)
unnamed: C34.1, U9.4 (BOOT)
unnamed: R12.1, R13.2, U9.7 (FB)
unnamed: R11.1, U9.6 (RT)
unnamed: C40.1, U10.4 (BOOT)
unnamed: R15.1, R16.2, U10.7 (FB)
unnamed: R14.1, U10.6 (RT)
VBAT: C28.1, C29.2, C31.1, C32.2, C35.1, C36.2, D3.1 (K), J8.2, U8.9 (EN), U8.10 (VIN), U8.11 (VIN_2), U8.12 (VIN_3), U9.9 (EN), U9.10 (VIN), U9.11 (VIN_2), U9.12 (VIN_3), U10.9 (EN), U10.10 (VIN), U10.11 (VIN_2), U10.12 (VIN_3); also elsewhere on the board

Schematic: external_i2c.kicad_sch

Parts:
J17: Conn_01x04_MountingPin; JST_SH_BM04B-SRSS-TB_1x04-1MP_P1.00mm_Vertical; LCSC C160390

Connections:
+3V3: J17.2; also elsewhere on the board
/MCU/I2C2_SCL: J17.4; also elsewhere on the board
/MCU/I2C2_SDA: J17.3; also elsewhere on the board
GND: J17.1; also elsewhere on the board

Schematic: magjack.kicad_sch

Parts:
J10: SI-60062-F; SI-60062-F_STW
R30, R31: 470; R_0402_1005Metric; LCSC C25117
U15: TPD4EUSB30; USON-10_2.5x1.0mm_P0.5mm; LCSC C5148477

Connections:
+3V3: J10.9 (ANODE), J10.11 (ANODE); also elsewhere on the board
/cm5/ETH_A+: J10.1 (TD+), U15.1 (D1+), U15.10 (NC); also elsewhere on the board
/cm5/ETH_A-: J10.3 (TD-), U15.2 (D1-), U15.9 (NC); also elsewhere on the board
/cm5/ETH_ACT: R31.2; also elsewhere on the board
/cm5/ETH_B+: J10.4 (RD+), U15.4 (D2+), U15.7 (NC); also elsewhere on the board
/cm5/ETH_B-: J10.6 (RD-), U15.5 (D2-), U15.6 (NC); also elsewhere on the board
/cm5/ETH_LINK: R30.2; also elsewhere on the board
ETH_SHIELD_GND: J10.15 (SH), J10.16 (SH)
GND: J10.8 (C), U15.3 (GND), U15.8 (GND); also elsewhere on the board
unnamed: J10.10 (CATHODE), R30.1
unnamed: J10.12 (CATHODE), R31.1

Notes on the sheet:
The NC pins can have signals routed through them

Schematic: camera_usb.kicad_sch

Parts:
J11: CU01SAH0S00; CONN_CU01SAH0S00_CVI
U16: TPD4EUSB30; USON-10_2.5x1.0mm_P0.5mm; LCSC C5148477

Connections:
+5V: J11.1 (VBUS); also elsewhere on the board
/cm5/Camera USB/D+: J11.3 (D+), U16.1 (D1+), U16.10 (NC); also elsewhere on the board
/cm5/Camera USB/D-: J11.2 (D-), U16.2 (D1-), U16.9 (NC); also elsewhere on the board
GND: J11.4 (GND), U16.3 (GND), U16.8 (GND); also elsewhere on the board

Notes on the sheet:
The NC pins can have signals routed through them

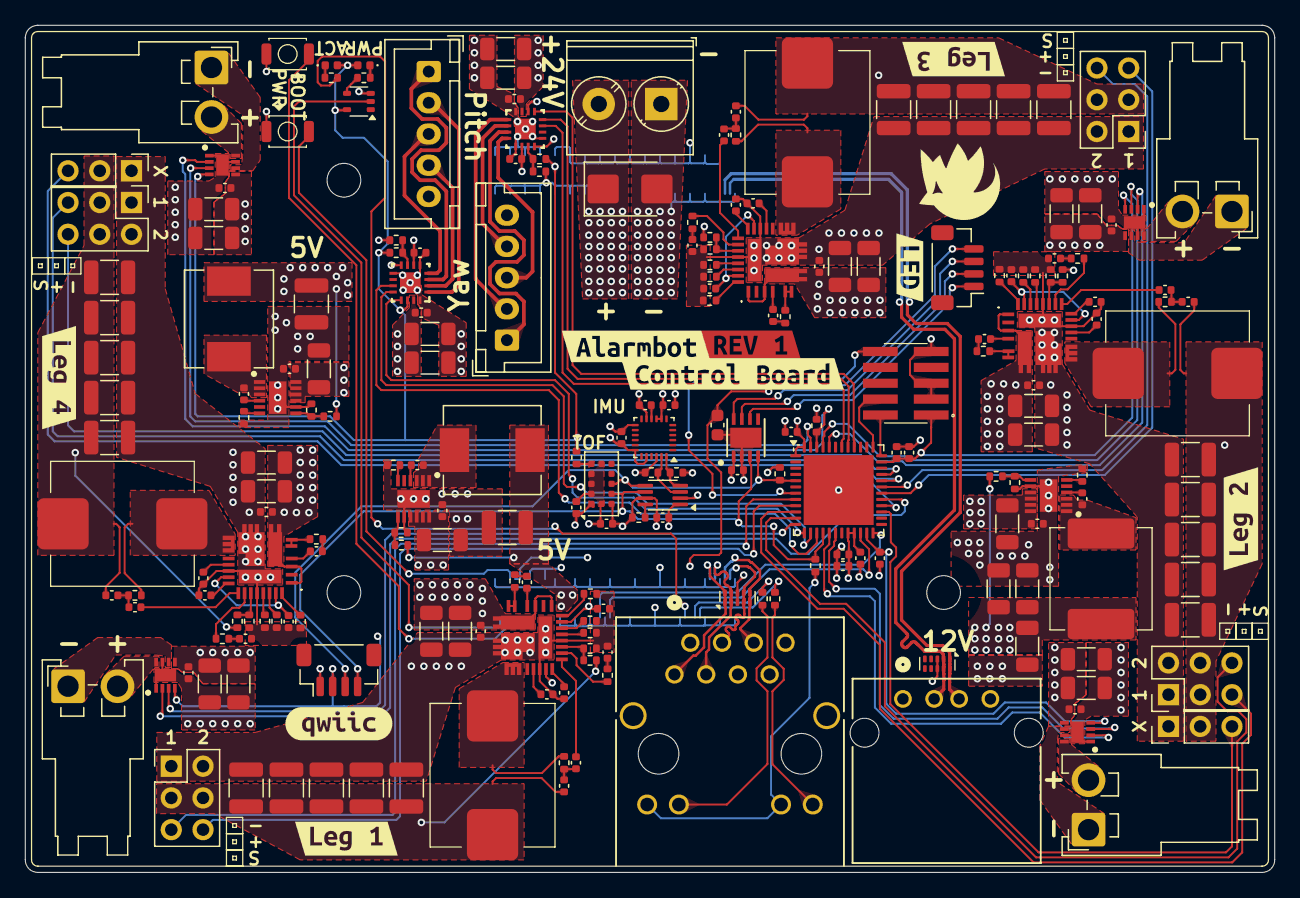
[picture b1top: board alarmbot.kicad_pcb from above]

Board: 4 copper layers, 100.0 x 67.8 mm, 226 parts (1 on the bottom side), 160 nets.

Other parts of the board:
kibuzzard-67D5DC35: G***; kibuzzard-67D5DC35
kibuzzard-67D5DC97: G***; kibuzzard-67D5DC97
kibuzzard-67D6EFDF: G***; kibuzzard-67D6EFDF
kibuzzard-67D6EFED: G***; kibuzzard-67D6EFED
kibuzzard-67D6F2AE: G***; kibuzzard-67D6F2AE
kibuzzard-67D6F2CD: G***; kibuzzard-67D6F2CD
kibuzzard-67D6F2E9: G***; kibuzzard-67D6F2E9
kibuzzard-67D6F300: G***; kibuzzard-67D6F300
kibuzzard-67D8C3DC: G***; kibuzzard-67D8C3DC

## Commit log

2025-03-19 Added custom libraries to pcb
2025-03-19 Cleaned up 3d model paths
2025-03-19 Added pcb render
2025-03-19 Added README.md
2025-03-29 Initialized firmware
2025-03-29 Added gitignore
2025-04-28 Added shared message format crate
